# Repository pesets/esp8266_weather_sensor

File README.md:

# esp8266_weather_sensor
Not expensive and low power consumption weather sensor, which was created on the microcontroller ESP8266.

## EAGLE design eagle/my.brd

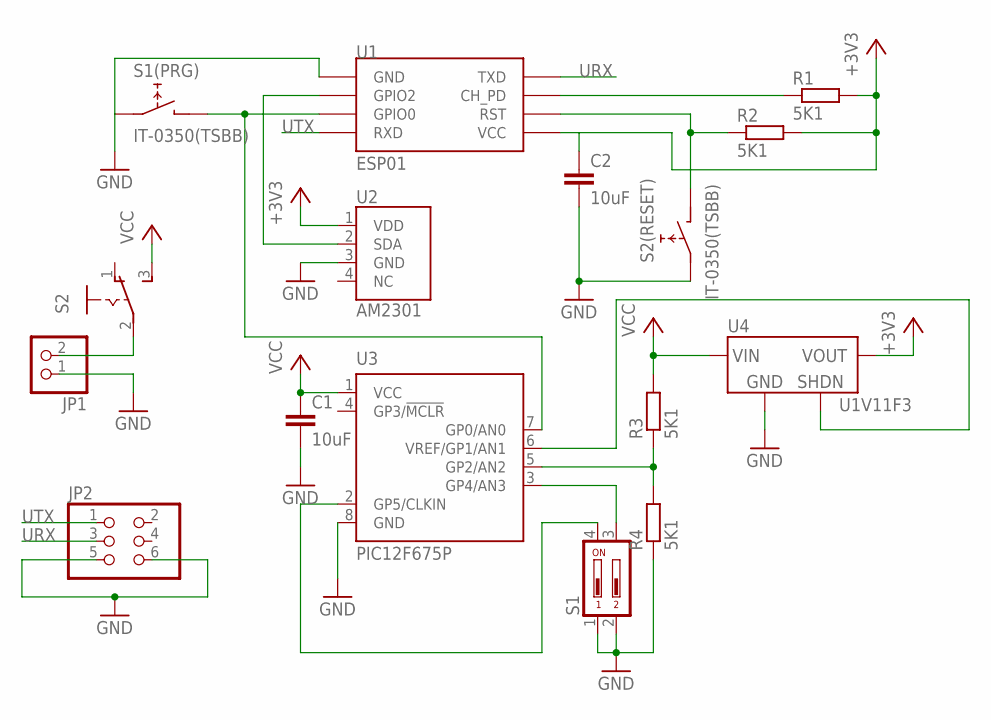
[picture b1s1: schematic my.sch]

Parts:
C1, C2: 10uF; C3216
JP1: PINHD-1X2/90; 1X02/90
JP2: PINHD-2X3; 2X03
R1, R2, R3, R4: 5K1; R3216
S1: DS02; DS-02
S1(PRG), S2(RESET): IT-0350(TSBB); TL1105L-4,3
S2: SS-12D00; M251
U1: ESP01
U2: AM2301; AM2301-NO-COVER
U3: PIC12F675P; DIL8
U4: U1V11F3; STEP-UP

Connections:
+3V3: C2.1, R1.2, R2.2, U1.VCC, U2.1 (VDD), U4.VOUT
GND: C1.2, C2.2, JP1.1, JP2.5, JP2.6, R4.1, S1.1, S1.2, S1(PRG).1, S2(RESET).1, U1.GND, U2.3 (GND), U3.8 (GND), U4.GND
unnamed: R3.1, R4.2, U3.5 (GP2/AN2)
unnamed: R2.1, S2(RESET).2, U1.RST
unnamed: S1(PRG).2, U1.GPIO0, U3.7 (GP0/AN0)
unnamed: U1.GPIO2, U2.2 (SDA)
unnamed: S1.4, U3.2 (GP5/CLKIN)
unnamed: S1.3, U3.3 (GP4/AN3)
unnamed: R1.1, U1.CH_PD
unnamed: U3.6 (VREF/GP1/AN1), U4.SHDN
unnamed: JP1.2, S2.2
URX: JP2.3, U1.TX (TXD)
UTX: JP2.1, U1.RX (RXD)
VCC: C1.1, R3.2, S2.3 (S), U3.1 (VCC), U4.VIN

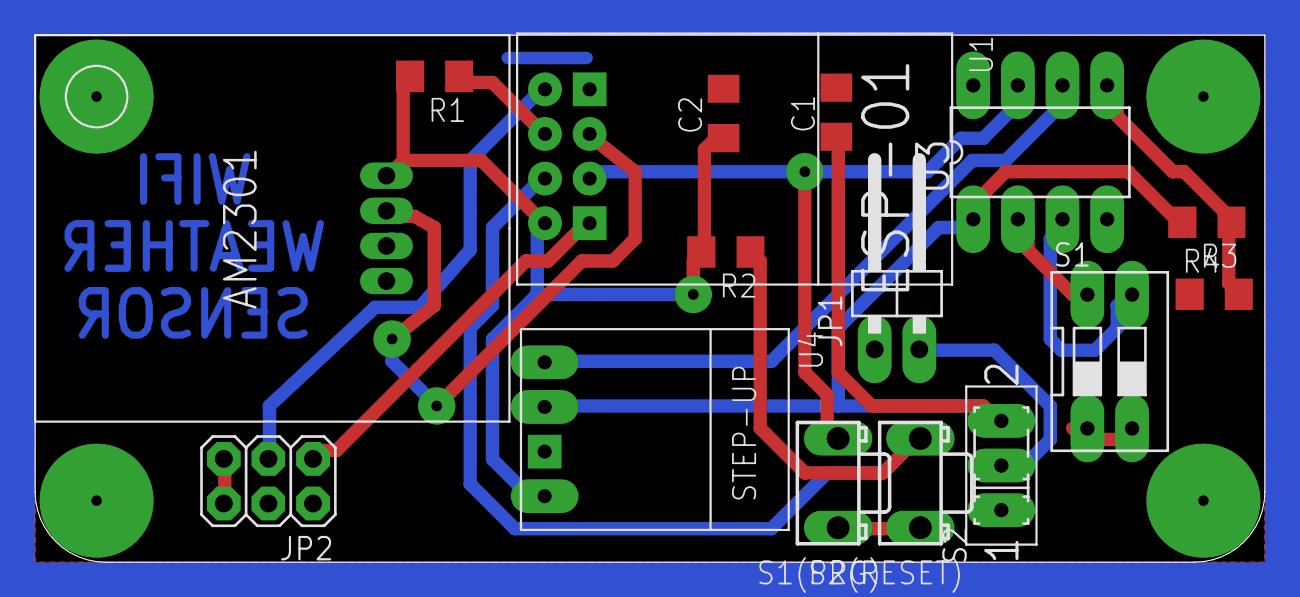
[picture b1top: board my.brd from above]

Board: 2 copper layers, 70.0 x 30.0 mm, 16 parts (0 on the bottom side), 14 nets.

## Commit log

2015-05-19 first upload
    first upload
2015-05-21 Schema of board
    Schema of board for EAGLE PCB Design Software
2015-05-25 SMP components and hand-made
    Switched to use SMP components and hand-made circuit board
